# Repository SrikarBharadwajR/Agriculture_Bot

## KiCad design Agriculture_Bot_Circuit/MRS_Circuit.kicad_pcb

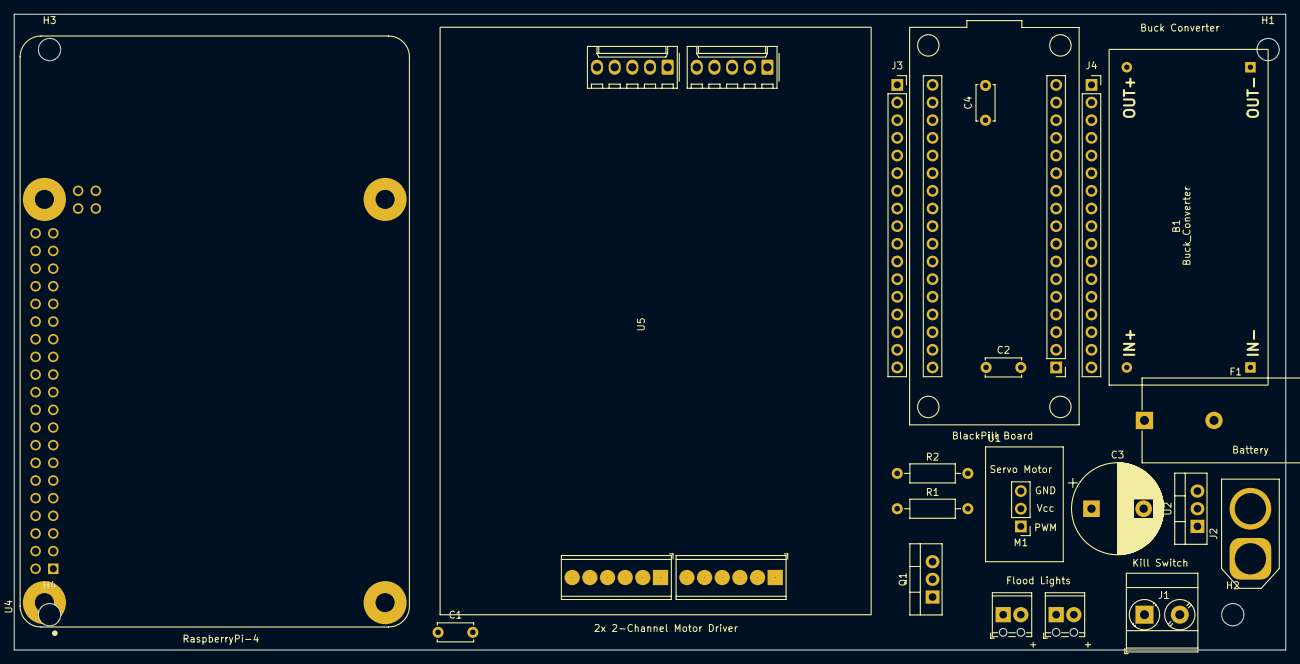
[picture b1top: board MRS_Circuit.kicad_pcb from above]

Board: 2 copper layers, 182.9 x 91.4 mm, 24 parts (0 on the bottom side), 13 nets, no tracks yet.

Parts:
B1: Buck_Converter; Buck_Converter_small
C1, C2, C4: 100nF; C_Disc_D5.0mm_W2.5mm_P5.00mm
C3: 10uF; CP_Radial_D13.0mm_P7.50mm
D1, D2: White; TerminalBlock_Phoenix_MPT-0,5-2-2.54_1x02_P2.54mm_Horizontal
F1: Fuse; Fuseholder_Cylinder-5x20mm_Schurter_FAB_0031-355x_Horizonta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
H1, H2, H3, H4: MountingHole; MountingHole_3.2mm_M3
J1: Kill-Switch; TerminalBlock_Phoenix_MKDS-3-2-5.08_1x02_P5.08mm_Horizontal
J2: Battery; AMASS_XT60-M_1x02_P7.20mm_Vertical
J3: BPDummy_L; PinSocket_1x17_P2.54mm_Vertical
J4: BPDummy_R; PinSocket_1x17_P2.54mm_Vertical
M1: Motor_Servo; PinHeader_1x03_P2.54mm_Vertical
Q1: IRF510PBF; TO-220-3_Vertical
R1: 100R; R_Axial_DIN0207_L6.3mm_D2.5mm_P10.16mm_Horizontal
R2: 10k; R_Axial_DIN0207_L6.3mm_D2.5mm_P10.16mm_Horizontal
U1: YAAJ_BlackPill; YAAJ_BlackPill_2
U2: AMS1117-3.3; TO-220-3_Vertical
U4: RASPBERRY_PI_4B_4GB; MODULE_RASPBERRY_PI_4B_4GB
U5: 2xMDD10A

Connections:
+3.3v: C2.1, C4.1, U1.16 (3V3), U2.2 (VO)
+5v: B1.4 (OUT+), C1.1, C3.1, U2.3 (VI), U4.2 (5V), U4.4 (5V)
+12v: B1.1 (IN+), D1.2 (A), J1.2, M1.2 (+), U5.3, U5.9
Bat_in: F1.1, J2.2
Flash_Lights: R1.1, R2.2, U1.28 (PA5)
GND: B1.2 (IN-), B1.3 (OUT-), C1.2, C2.2, C3.2, C4.2, J2.1, M1.3 (-), Q1.3 (S), R2.1, U1.17 (GND), U1.18 (GND), U2.1 (GND), U4.6 (GND), U4.9 (GND), U4.14 (GND), U4.20 (GND), U4.25 (GND), U4.30 (GND), U4.34 (GND), U4.39 (GND), U5.4, U5.10
unnamed: D1.1 (K), D2.2 (A)
unnamed: D2.1 (K), Q1.2 (D)
unnamed: F1.2, J1.1
unnamed: Q1.1 (G), R1.2
RxBP: U1.6 (PA9), U4.10 (GPIO15/RXD0)
Servo_Ctrl: M1.1 (PWM), U1.26 (PA3)
TxBP: U1.7 (PA10), U4.8 (GPIO14/TXD0)

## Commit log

2023-11-17 Circuit
